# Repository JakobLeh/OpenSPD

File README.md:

# OpenSPD

**OpenSPD** (Open-Source Single Photon Detector) is a hardware project for detecting single photons in the near-infrared (NIR) range, specifically designed for applications such as photonic side-channel analysis using hot-carrier luminescence (HCL) from integrated circuits. The project is centered around a compact, low-cost, and high-sensitivity InGaAs avalanche photodiode (APD).

This repository contains the full open-source hardware files including:

- 🧩 **KiCad project files** (schematics, layout)
- 📦 **Bill of Materials (BOM)**
- 📚 **Custom libraries**
- 🧾 Supporting documentation

## Features

- **Avalanche Photodiode (APD)**: Excelitas C30645L-080 for high NIR sensitivity.
- **Bias Supply**: Adjustable high-voltage bias using MAX1932 DC-DC converter.
- **Transimpedance Amplifier (TIA)**: High-speed current-to-voltage conversion using the AD8015.
- **Gate Input**: Supports (sinusoidal, square-wave) gated operation for time-selective photon detection.
- **Passive Quenching**: Simple passive quenching resistor for avalanche suppression.
- **Mechanical Mounting Interface**: Compatible with free-space optical setups

### Front Side

### Back Side

Date: May 2025

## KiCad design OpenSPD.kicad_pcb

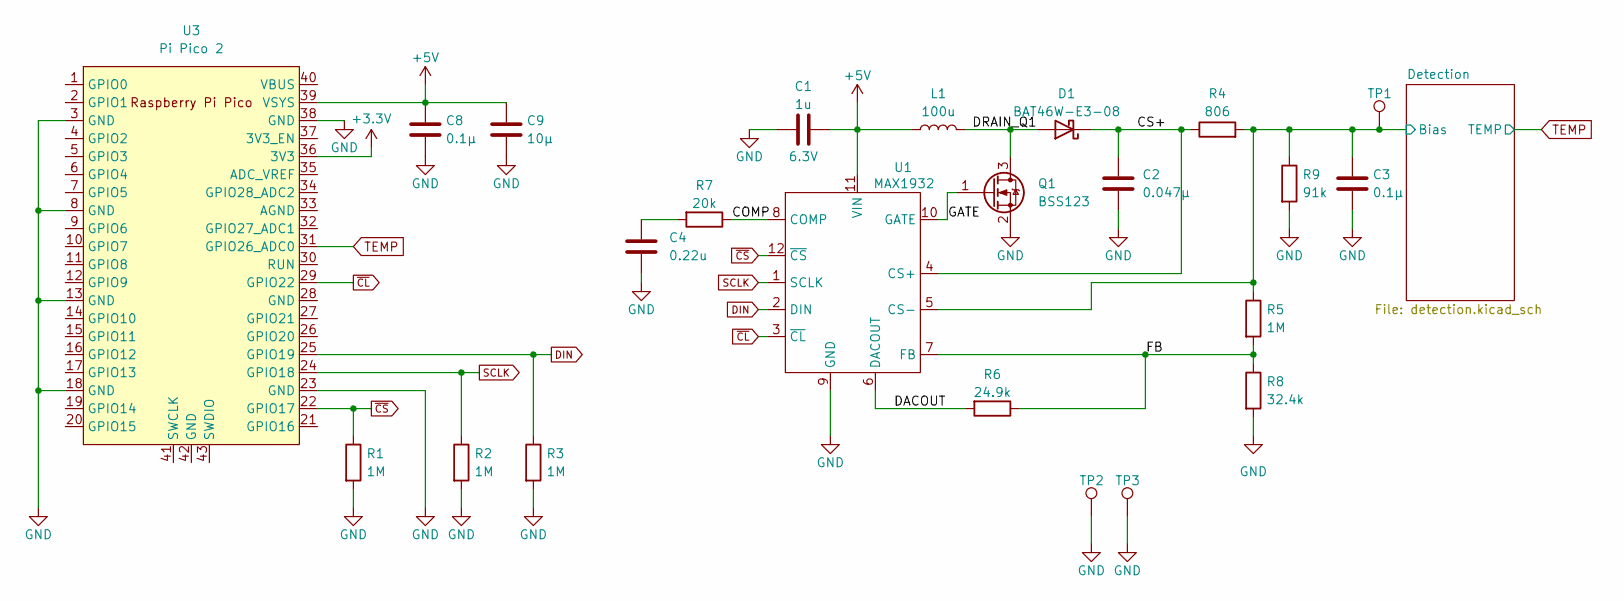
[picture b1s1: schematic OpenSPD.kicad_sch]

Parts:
C1: 1u; C_0805_2012Metric; Voltage 6.3V
C2: 0.047µ; C_0805_2012Metric
C3, C8: 0.1µ; C_0805_2012Metric
C4: 0.22u; C_0805_2012Metric
C9: 10µ; C_0805_2012Metric
D1: BAT46W-E3-08; SOD-123; DigiKey Part Number BAT46W-E3-08TR-ND
L1: 100u; 100µ_L
Q1: BSS123; SOT-23; DigiKey Part Number BSS123NTR-ND
R1, R2, R3, R5: 1M; 0805_2012_Vishay
R4: 806; 0805_2012_Vishay
R6: 24.9k; 0805_2012_Vishay
R7: 20k; 0805_2012_Vishay
R8: 32.4k; 0805_2012_Vishay
R9: 91k; 0805_2012_Vishay
TP1, TP2, TP3: TestPoint; TestPoint_Keystone_5002; DigiKey Part Number 445-2554-2-ND
U1: MAX1932; T1244-4; DigiKey Part Number MAX1932ETC+TTR-ND
U3: Pi Pico 2; RPi_Pico_SMD_TH

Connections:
+3.3V: U3.36 (3V3); also elsewhere on the board
+5V: C1.2, C8.1, C9.1, L1.1, U1.11 (VIN), U3.39 (VSYS); also elsewhere on the board
/COMP: R7.1, U1.8 (COMP)
/CS+: C2.1, D1.1 (K), R4.1, U1.4 (CS+)
/DACOUT: R6.2, U1.6 (DACOUT)
/DRAIN_Q1: D1.2 (A), L1.2, Q1.3 (D)
/Detection/Bias: C3.1, R4.2, R5.1, R9.1, TP1.1, U1.5 (CS-); also elsewhere on the board
/FB: R5.2, R6.1, R8.1, U1.7 (FB)
/GATE: Q1.1 (G), U1.10 (GATE)
DIN: R3.1, U1.2 (DIN), U3.25 (GPIO19)
GND: C1.1, C2.2, C3.2, C4.2, C8.2, C9.2, Q1.2 (S), R1.2, R2.2, R3.2, R8.2, R9.2, TP2.1, TP3.1, U1.9 (GND), U3.3 (GND), U3.8 (GND), U3.13 (GND), U3.18 (GND), U3.23 (GND), U3.38 (GND); also elsewhere on the board
unnamed: C4.1, R7.2
SCLK: R2.1, U1.1 (SCLK), U3.24 (GPIO18)
TEMP: U3.31 (GPIO26_ADC0); also elsewhere on the board
~CL: U1.3 (~CL), U3.29 (GPIO22)
~CS: R1.1, U1.12 (~CS), U3.22 (GPIO17)

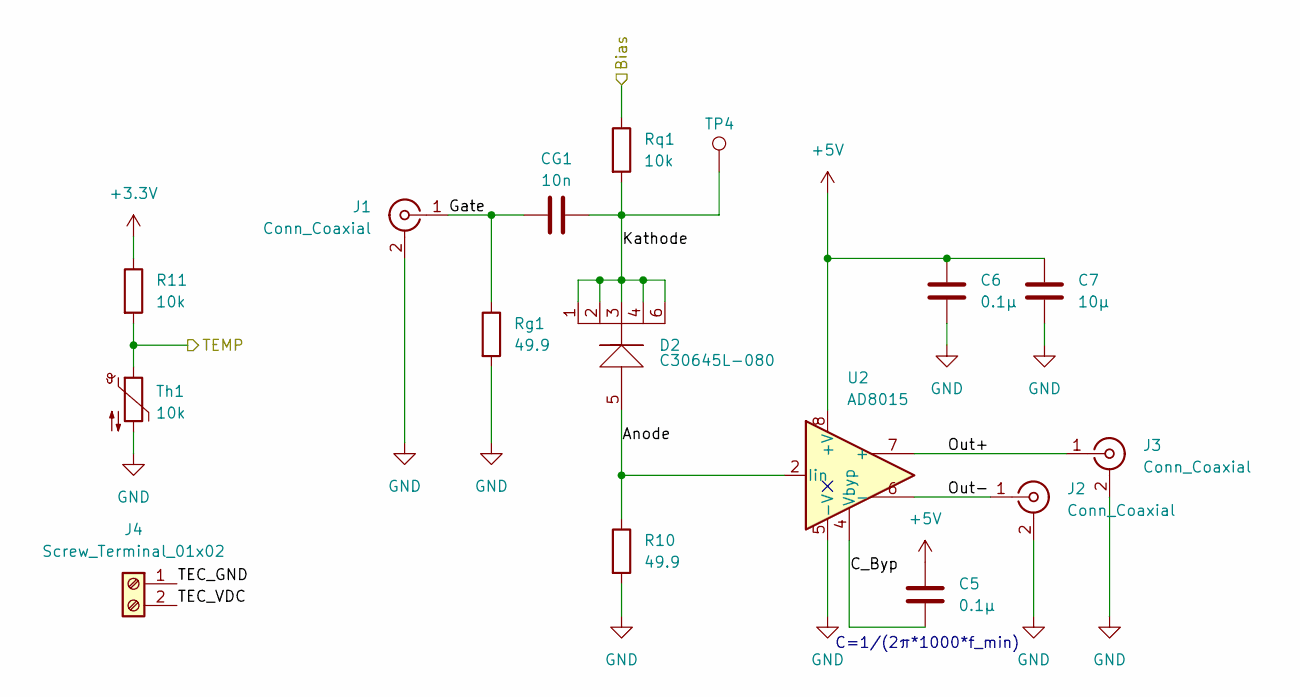
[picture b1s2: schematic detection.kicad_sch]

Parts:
C5, C6: 0.1µ; C_0805_2012Metric
C7: 10µ; C_0805_2012Metric
CG1: 10n; C_0805_2012Metric
D2: C30645L-080; DigiKey Part Number 1601-C30645L-080-ND
J1, J2, J3: Conn_Coaxial; SMA_Molex_73251-1153_EdgeMount_Horizontal; DigiKey Part Number 900-0732511153-ND
J4: Screw_Terminal_01x02; TerminalBlock_Phoenix_PT-1,5-2-5.0-H_1x02_P5.00mm_Horizontal; DigiKey Part Number 277-16667-ND
R10: 49.9; 0805_2012_Vishay
R11: 10k; 0805_2012_Vishay
Rg1: 49.9; 0805_2012_Vishay
Rq1: 10k; 0805_2012_Vishay
TP4: TestPoint; TestPoint_Keystone_5019_Minature; DigiKey Part Number 36-5019TR-ND
Th1: 10k; R_0603_1608Metric
U2: AD8015; SOIC-8_3.9x4.9mm_P1.27mm; DigiKey Part Number 505-AD8015ARZ-ND

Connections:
+3.3V: R11.1; also elsewhere on the board
+5V: C5.1, C6.1, C7.1, U2.8 (+V); also elsewhere on the board
/Detection/Anode: D2.5, R10.1, U2.2 (Iin)
/Detection/Bias: Rq1.1; also elsewhere on the board
/Detection/C_Byp: C5.2, U2.4 (Vbyp)
/Detection/Gate: CG1.1, J1.1 (In), Rg1.1
/Detection/Kathode: CG1.2, D2.1, D2.2, D2.3, D2.4, D2.6, Rq1.2, TP4.1
/Detection/Out+: J3.1 (In), U2.7 (+)
/Detection/Out-: J2.1 (In), U2.6 (-)
/Detection/TEC_GND: J4.1; also elsewhere on the board
/Detection/TEC_VDC: J4.2; also elsewhere on the board
GND: C6.2, C7.2, J1.2 (Ext), J2.2 (Ext), J3.2 (Ext), R10.2, Rg1.2, Th1.2, U2.5 (-V); also elsewhere on the board
TEMP: R11.2, Th1.1; also elsewhere on the board

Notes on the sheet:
C=1/(2π*1000*f_min)

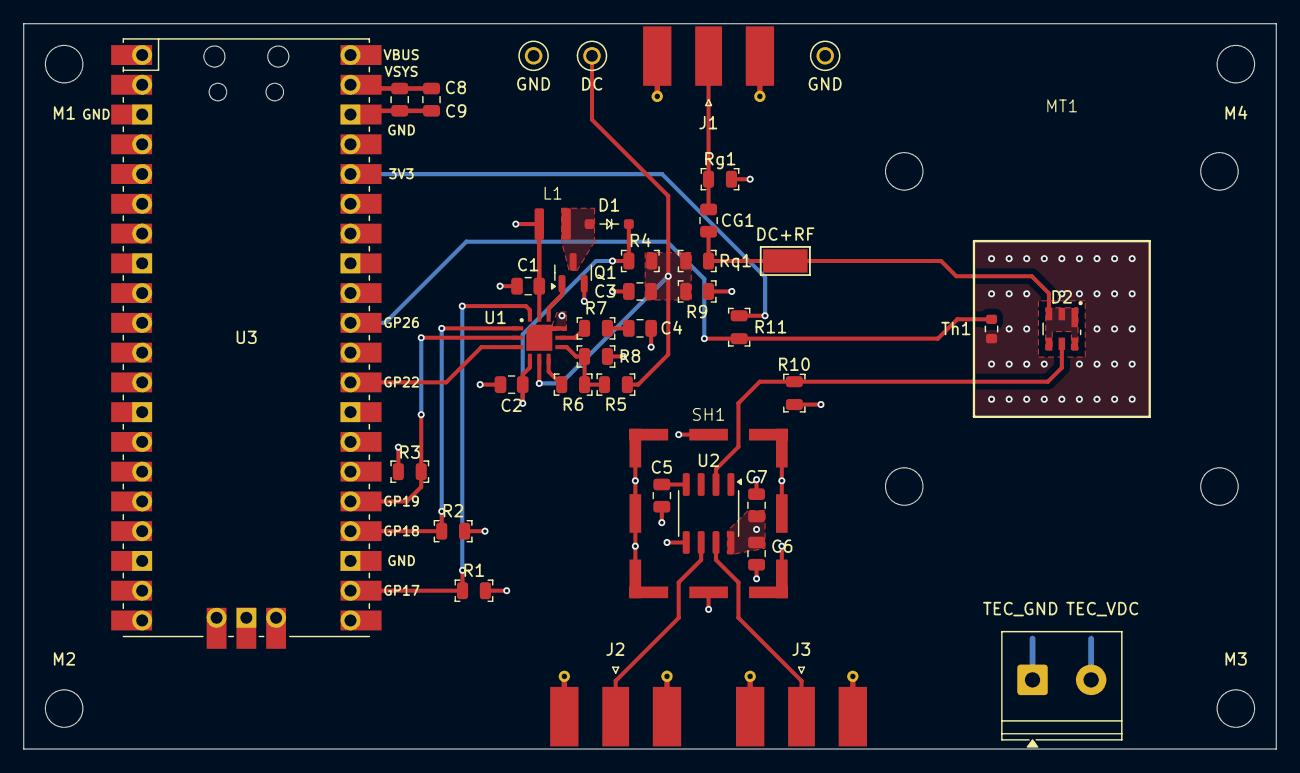
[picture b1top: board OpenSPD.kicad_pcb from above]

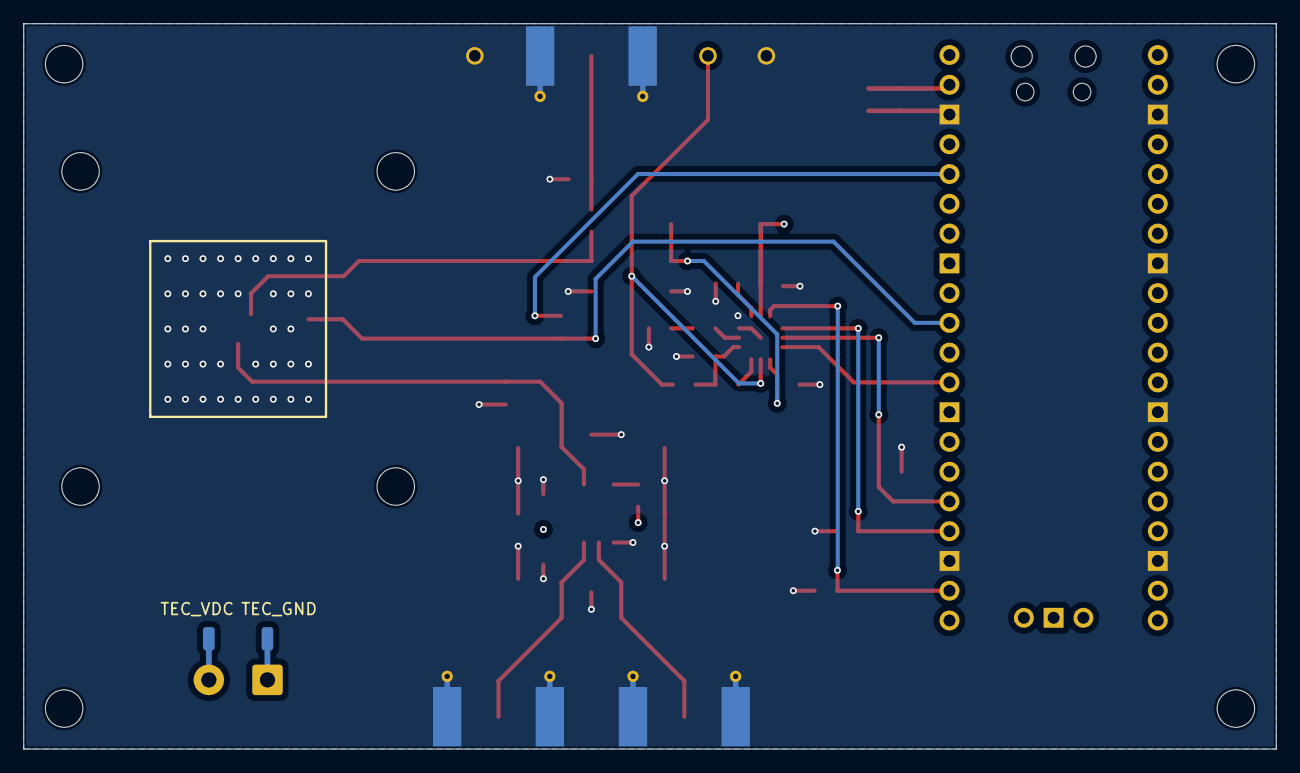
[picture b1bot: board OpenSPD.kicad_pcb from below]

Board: 4 copper layers, 106.9 x 61.9 mm, 47 parts (2 on the bottom side), 24 nets.

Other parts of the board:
M1, M2, M3, M4: MountingHole_3.2mm_M3
MT1: SM1F2
SH1: Shield_3610213126S
TEC_GND: SolderWirePad_1x01_SMD_1x2mm
TEC_VDC: SolderWirePad_1x01_SMD_1x2mm

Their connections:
/Detection/TEC_GND: TEC_GND.1; also elsewhere on the board
/Detection/TEC_VDC: TEC_VDC.1; also elsewhere on the board
GND: SH1.1; also elsewhere on the board
